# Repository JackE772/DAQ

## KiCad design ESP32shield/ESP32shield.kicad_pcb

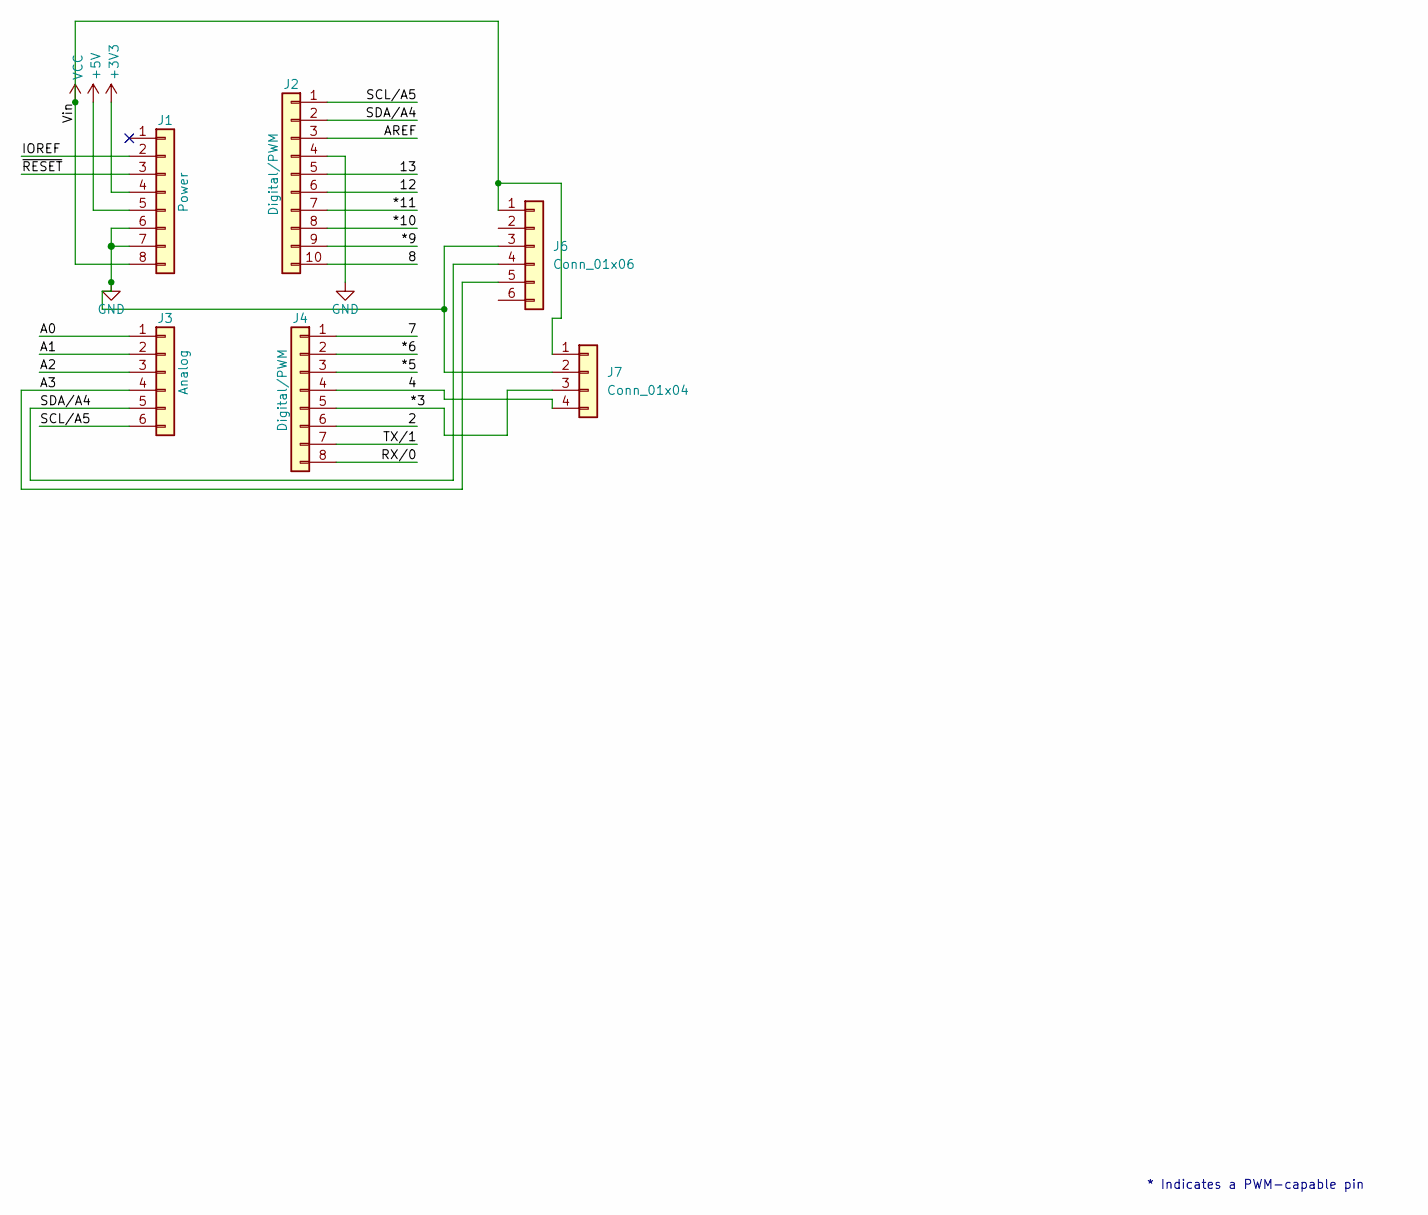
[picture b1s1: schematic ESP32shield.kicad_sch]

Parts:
J1: Power; PinSocket_1x08_P2.54mm_Vertical
J2: Digital/PWM; PinSocket_1x10_P2.54mm_Vertical
J3: Analog; PinSocket_1x06_P2.54mm_Vertical
J4: Digital/PWM; PinSocket_1x08_P2.54mm_Vertical
J6: Conn_01x06; PinHeader_1x06_P1.00mm_Vertical
J7: Conn_01x04; PinHeader_1x04_P1.00mm_Vertical

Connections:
+3V3: J1.4
+5V: J1.5
/2: J4.6
/4: J4.4, J7.4
/7: J4.1
/8: J2.10
/12: J2.6
/13: J2.5
/*3: J4.5, J7.3
/*5: J4.3
/*6: J4.2
/*9: J2.9
/*10: J2.8
/*11: J2.7
/A0: J3.1
/A1: J3.2
/A2: J3.3
/A3: J3.4, J6.5
/AREF: J2.3
/IOREF: J1.2
/RX/0: J4.8
/SCL/A5: J2.1, J3.6
/SDA/A4: J2.2, J3.5, J6.4
/TX/1: J4.7
/~RESET: J1.3
GND: J1.6, J1.7, J2.4, J6.3, J7.2
VCC: J1.8, J6.1, J7.1

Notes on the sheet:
* Indicates a PWM-capable pin

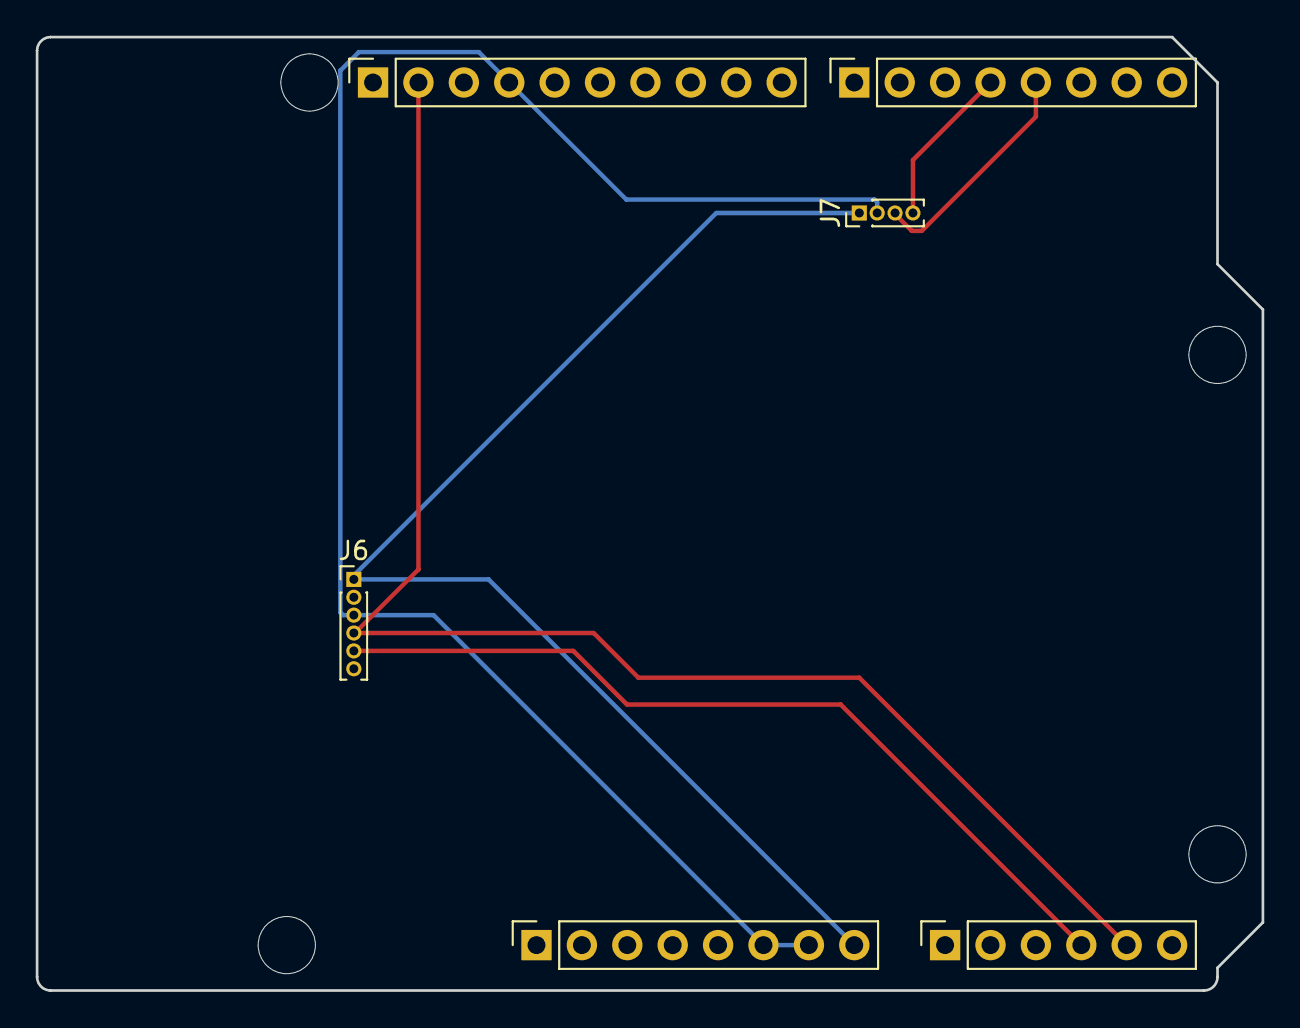
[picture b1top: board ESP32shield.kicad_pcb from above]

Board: 2 copper layers, 68.6 x 53.3 mm, 10 parts (0 on the bottom side), 7 nets.

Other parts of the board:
MH1, MH2, MH3, MH4: MountingHole_3.2mm

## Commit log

2024-11-06 added arduino code to github
2024-11-06 test commit
2024-11-08 Hey put some test Data and spreadsheet Bro
2024-11-13 minor changes to detector
2024-11-15 added z, pich, roll axis
2024-11-20 added GPS reading and loging
2024-11-21 Committed bros
2025-09-09 Add files via upload
    KiCad model for the shield
2025-09-23 ESP shield
    shield gerbers
2025-10-16 major reqwrites of the DAQ_main.ino file to improve functionality and fix bugs.
2025-10-18 BLE :)
2025-10-19 Velocity & Position now based on GPS and IMU data
    When GPS is active the velocity and position data should be corrected by the GPS
    There is also some shit going on with orientation to make the acceleration more accurate
2025-10-30 data files
2025-10-30 commemts updates
2025-10-30 data prossesing code started
2025-10-30 Start of GUI
2025-10-30 shield changes idk what changed but im committing it
2025-10-31 convert GPSDisplay file to a .py
2025-11-06 Display long and lat and imu data
2025-12-02 moved some code around all chill
2025-12-04 hello hi
2025-12-04 all GUI changes
2025-12-04 Starting getting data and maybe displaying it
2025-12-04 Make gui console log ble info grabber
2025-12-04 Added start of speedometer
2026-01-02 added requirements.txt file for GUI dependencies
2026-01-02 chagned layout a bit to add speedometer widget to the right side
2026-02-03 added GPS tracking with speed and speedometer updates
2026-02-03 Speedometer update
2026-02-03 Colors!
2026-02-03 wrong piece of data...
2026-02-03 Imu data yippee!!!
2026-02-03 file to large
2026-02-10 minor UI changes
2026-02-10 Refactor of gps display
2026-02-12 added accel chart
2026-02-24 main player
2026-03-03 more gps unborking
2026-03-10 Thanks chat for the numbers on the chart
2026-03-24 visual changes
2026-03-24 changed acceleration from tuple to float
2026-03-24 minor rework for new IMU
2026-03-31 Cleaner display
2026-03-31 BIIG CHANGES
2026-04-06 idk what is changed in this version but I guess I will push it
2026-04-07 Closer to getting imu working
2026-04-16 BIIIIG push
2026-04-24 push
2026-04-24 fart
2026-04-24 WE ARE SO CLOSE
